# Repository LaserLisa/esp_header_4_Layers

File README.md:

KiCad version: 10.0

4-layer PCB board designed as header for ESP32-S3 developer board to interface up to 15 motors and 15 analog sensors.

Top Layer: 	Components and analog signals

Layer 1:		GND plane

Layer 2: 		6V Power plane

Bottom layer: 	3V power and digital signals

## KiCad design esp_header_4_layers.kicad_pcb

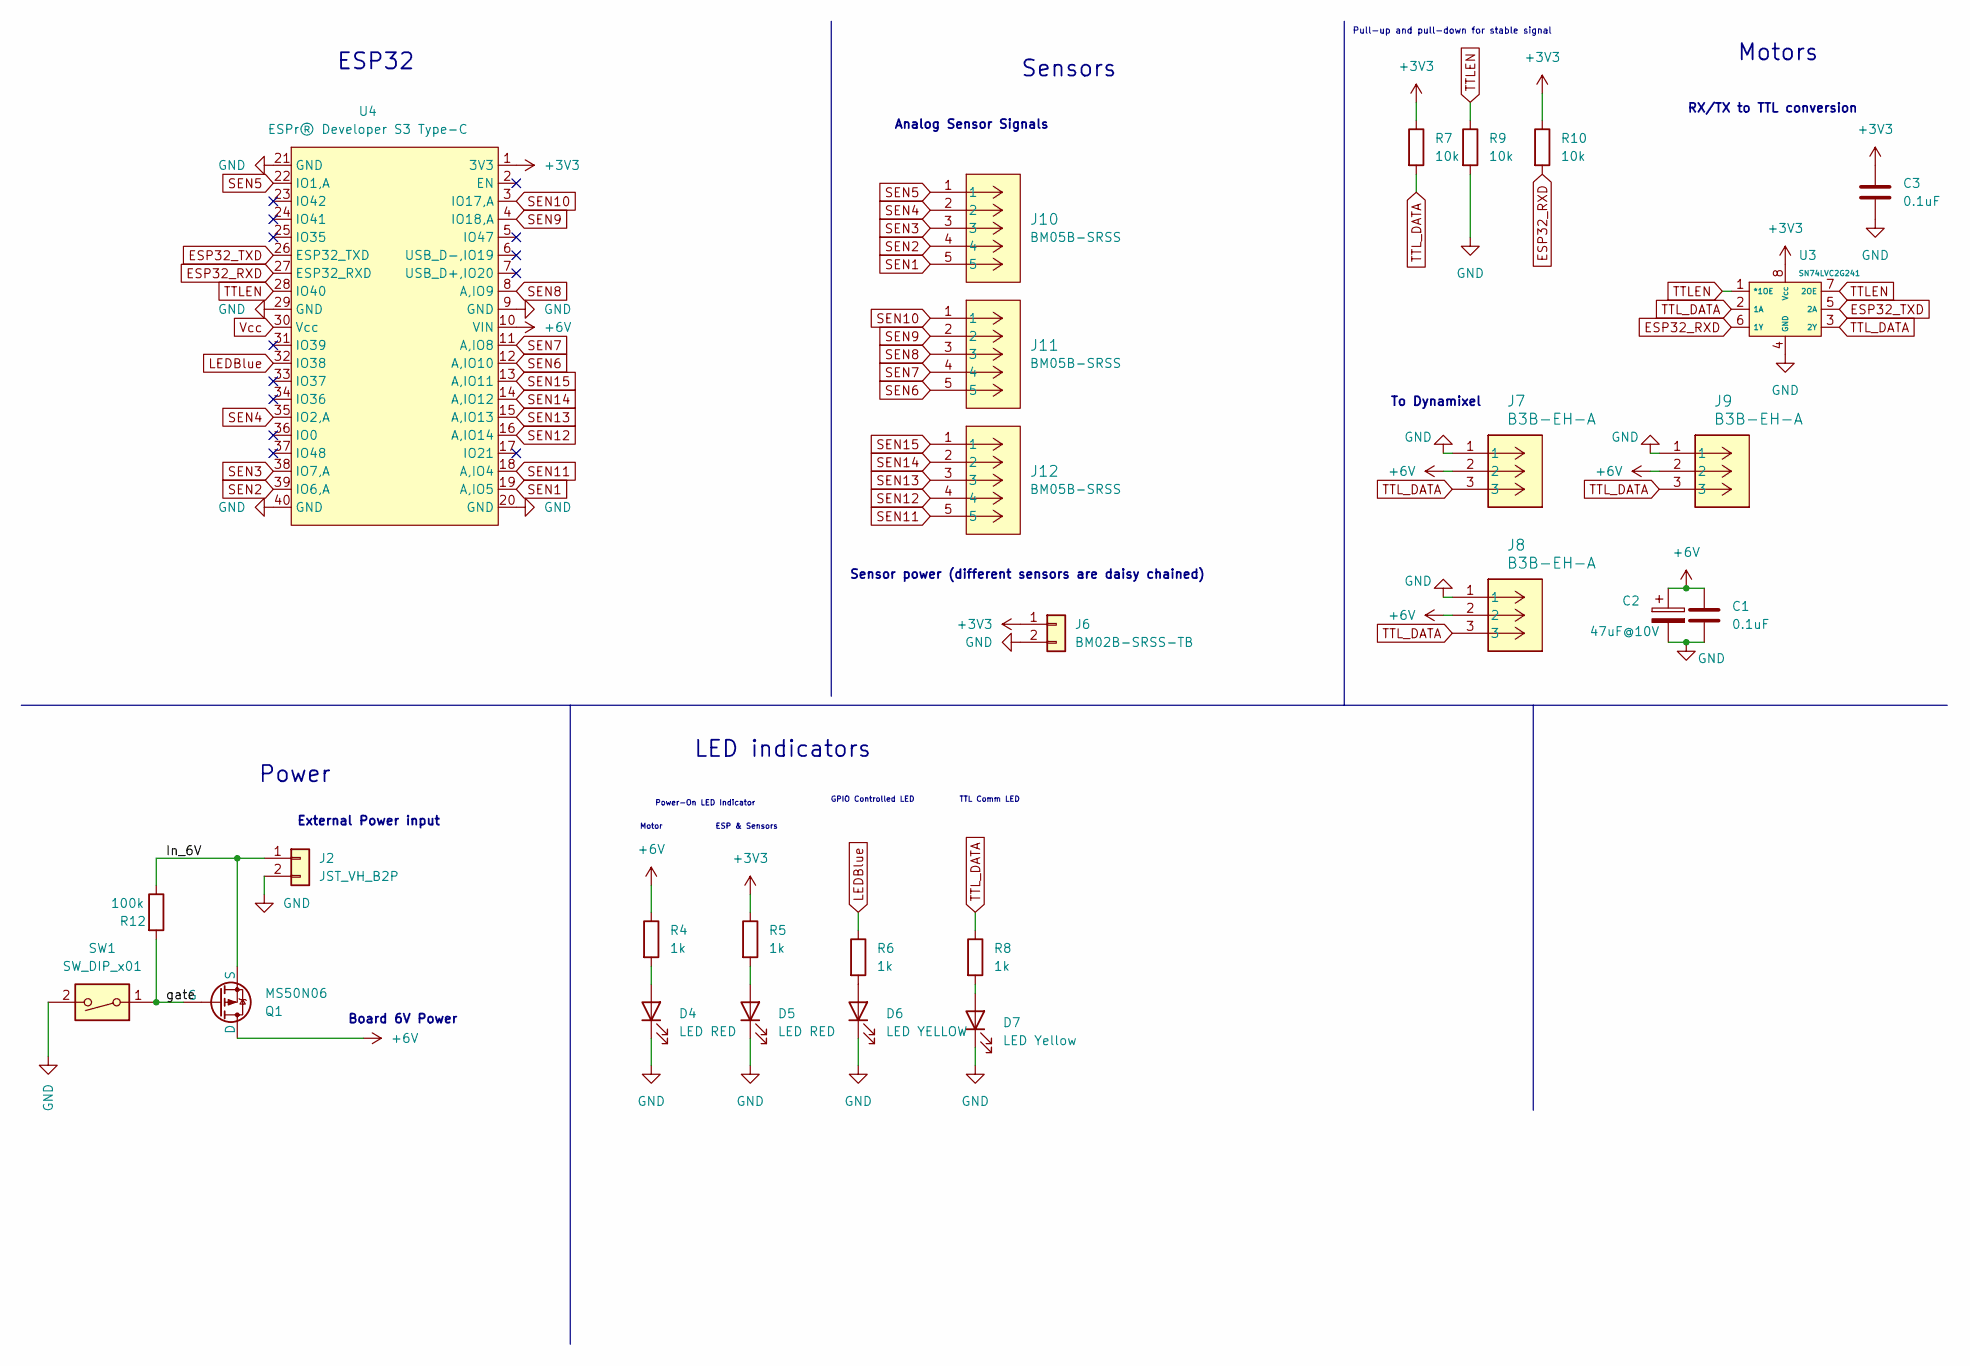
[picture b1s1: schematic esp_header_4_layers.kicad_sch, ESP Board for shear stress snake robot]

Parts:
C1, C3: 0.1uF; C_0603_1608Metric; JLCPCB Part# C14663
C2: 47uF@10V; C_1206_3216Metric; JLCPCB Part# C96123
D4, D5: LED RED; LED_0603_1608Metric; JLCPCB Part# C2286
D6: LED YELLOW; LED_0603_1608Metric; JLCPCB Part# C89811
D7: LED Yellow; LED_0603_1608Metric; JLCPCB Part# C89811
J2: JST_VH_B2P; JST_VH_B2P-VH_1x02_P3.96mm_Vertical
J6: BM02B-SRSS-TB; JST_BM02B-SRSS-TB; JLCPCB Part# C160388
J7, J8, J9: B3B-EH-A; JST-B3B-EH-A
J10, J11, J12: BM05B-SRSS; JST_BM05B-SRSS-TB; JLCPCB Part# C160391
Q1: MS50N06; TO-252-2; JLCPCB Part# C2902884
R4, R5, R6, R8: 1k; R_0603_1608Metric; JLCPCB Part# C21190
R7, R9, R10: 10k; R_0603_1608Metric; JLCPCB Part# C25804
R12: 100k; R_0603_1608Metric; JLCPCB Part# C25803
SW1: SW_DIP_x01; SW_DIP_SPSTx01_Slide_6.7x4.1mm_W6.73mm_P2.54mm_LowProfile_J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
U3: SN74LVC2G241; SN74LV2G241DCUR; JLCPCB Part# SN74LVC2G241DCUR
U4: ESPr® Developer S3 Type-C; ESP32-S3 dev board

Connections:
+3V3: C3.1, J6.1, R5.1, R7.1, R10.1, U3.8 (Vcc), U4.1 (3V3)
+6V: C1.1, C2.1, J7.2, J8.2, J9.2, Q1.D, R4.1, U4.10 (VIN)
/In_6V: J2.1, Q1.S, R12.1
/gate: Q1.G, R12.2, SW1.1
ESP32_RXD: R10.2, U3.6 (1Y), U4.27 (ESP32_RXD)
ESP32_TXD: U3.5 (2A), U4.26 (ESP32_TXD)
GND: C1.2, C2.2, C3.2, D4.1 (K), D5.1 (K), D6.1 (K), D7.1 (K), J2.2, J6.2, J7.1, J8.1, J9.1, R9.2, SW1.2, U3.4 (GND), U4.9 (GND), U4.20 (GND), U4.21 (GND), U4.29 (GND), U4.40 (GND)
LEDBlue: R6.1, U4.32 (IO38)
unnamed: D4.2 (A), R4.2
unnamed: D5.2 (A), R5.2
unnamed: D6.2 (A), R6.2
unnamed: D7.2 (A), R8.2
SEN1: J10.5, U4.19 (A,IO5)
SEN2: J10.4, U4.39 (IO6,A)
SEN3: J10.3, U4.38 (IO7,A)
SEN4: J10.2, U4.35 (IO2,A)
SEN5: J10.1, U4.22 (IO1,A)
SEN6: J11.5, U4.12 (A,IO10)
SEN7: J11.4, U4.11 (A,IO8)
SEN8: J11.3, U4.8 (A,IO9)
SEN9: J11.2, U4.4 (IO18,A)
SEN10: J11.1, U4.3 (IO17,A)
SEN11: J12.5, U4.18 (A,IO4)
SEN12: J12.4, U4.16 (A,IO14)
SEN13: J12.3, U4.15 (A,IO13)
SEN14: J12.2, U4.14 (A,IO12)
SEN15: J12.1, U4.13 (A,IO11)
TTLEN: R9.1, U3.1 (*1OE), U3.7 (2OE), U4.28 (IO40)
TTL_DATA: J7.3, J8.3, J9.3, R7.2, R8.1, U3.2 (1A), U3.3 (2Y)
Vcc: U4.30 (Vcc)

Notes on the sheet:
RX/TX to TTL conversion
Sensor power (different sensors are daisy chained)
Power
ESP32
Board 6V Power
TTL Comm LED
Power-On LED Indicator
Motor
External Power input
To Dynamixel
LED indicators
Analog Sensor Signals
Motors
ESP & Sensors
Sensors
Pull-up and pull-down for stable signal
GPIO Controlled LED

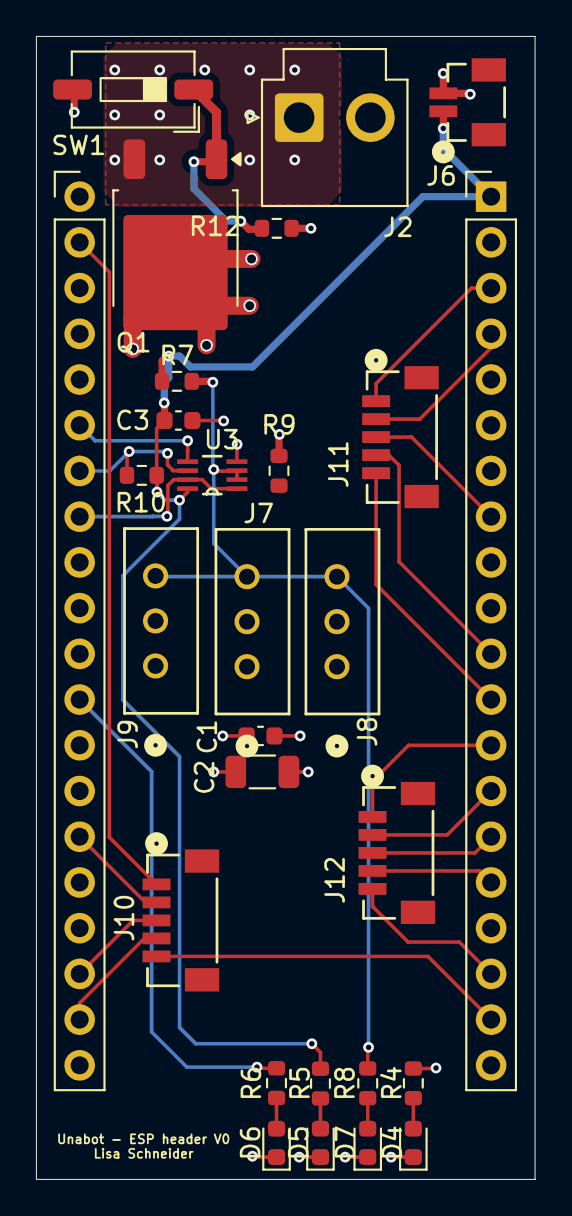
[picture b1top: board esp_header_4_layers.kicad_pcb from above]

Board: 4 copper layers, 27.7 x 63.5 mm, 27 parts (0 on the bottom side), 29 nets.

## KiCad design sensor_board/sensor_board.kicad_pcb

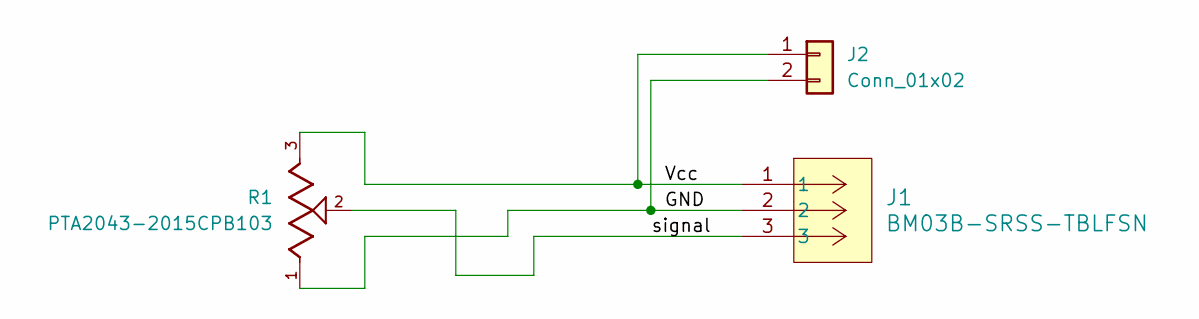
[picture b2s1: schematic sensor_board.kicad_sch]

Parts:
J1: BM03B-SRSS-TBLFSN; CONN_BM03B-SRSS-TBLFSN_JST
J2: Conn_01x02; JST_EH_S2B-EH_1x02_P2.50mm_Horizontal
R1: PTA2043-2015CPB103; PARTREV 04/21

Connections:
/GND: J1.2, J2.2, R1.1
/Vcc: J1.1, J2.1, R1.3
/signal: J1.3, R1.2

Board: 2 copper layers, 3 parts (0 on the bottom side), 3 nets, no tracks yet.

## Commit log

2026-05-07 untracked unnecessary files
2026-05-07 added gitignore
2026-05-07 remove gbrjob and kicad_prl from tracking
2026-05-07 removed lck files from tracking
2026-05-07 untrack backups
2026-05-07 Add project description and KiCad version to README
2026-05-07 made schematic clearer
2026-05-07 changed to PMOS instead of NMOS
2026-05-07 via size
2026-05-07 added model for pmos
